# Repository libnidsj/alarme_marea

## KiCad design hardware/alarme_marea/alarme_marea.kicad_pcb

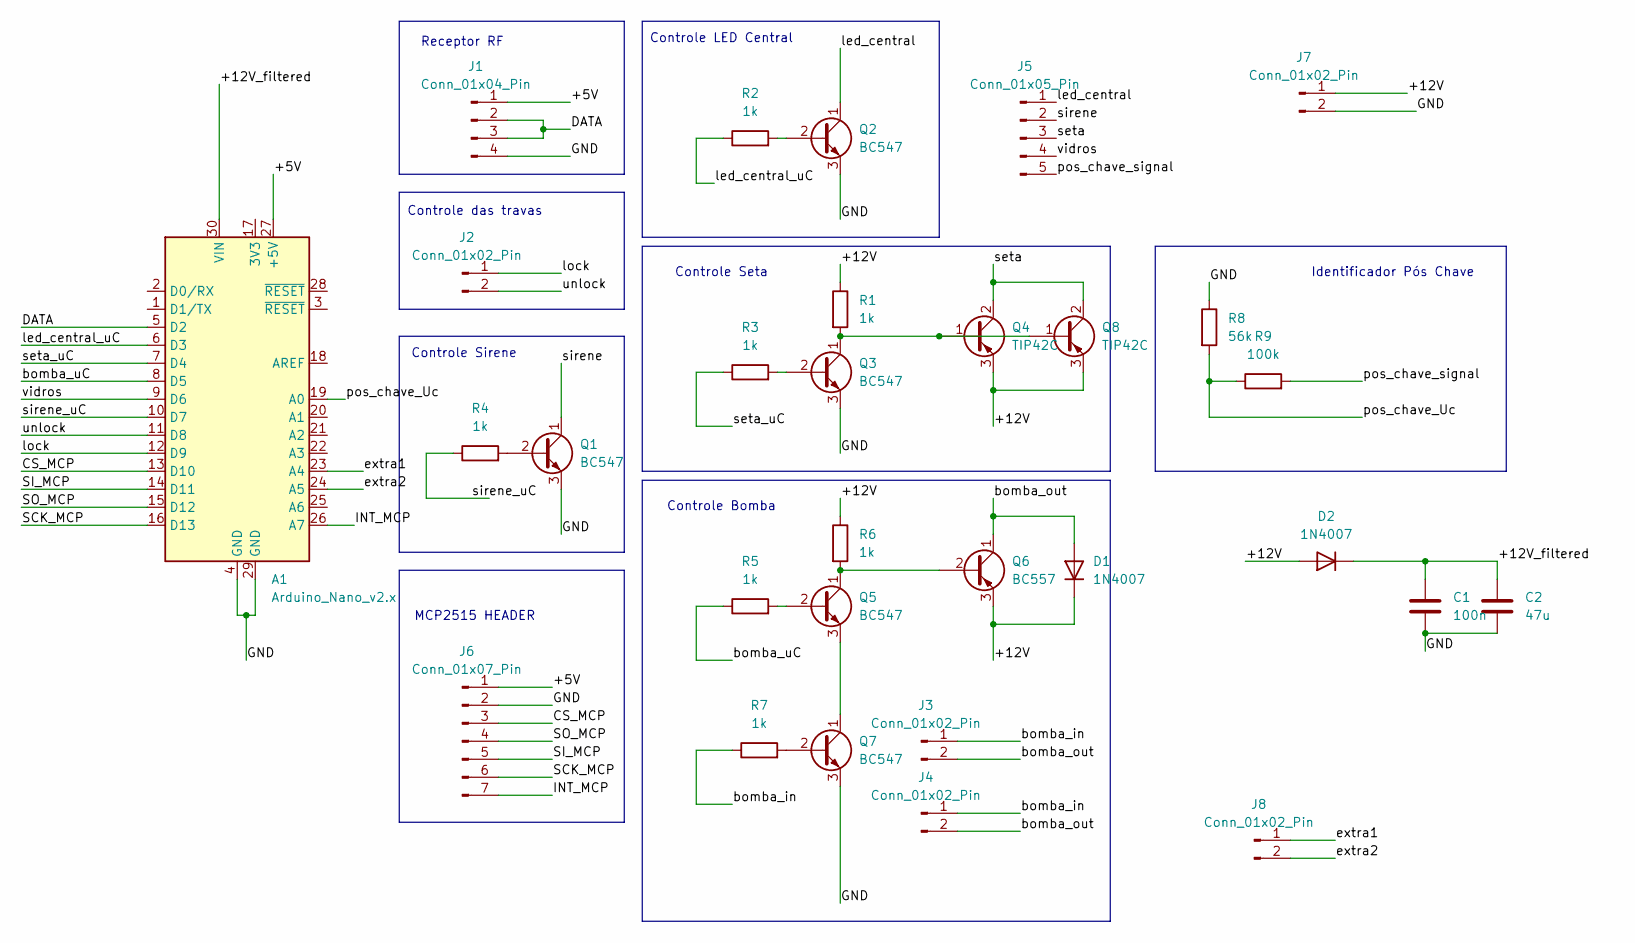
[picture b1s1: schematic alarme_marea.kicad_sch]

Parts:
A1: Arduino_Nano_v2.x; Arduino_Nano
C1: 100n; C_Disc_D5.0mm_W2.5mm_P5.00mm
C2: 47u; CP_Radial_D10.0mm_P5.00mm
D1, D2: 1N4007; D_DO-41_SOD81_P10.16mm_Horizontal
J1: Conn_01x04_Pin; PinSocket_1x04_P2.54mm_Vertical
J2, J3, J4, J7, J8: Conn_01x02_Pin; PinSocket_1x02_P2.54mm_Vertical
J5: Conn_01x05_Pin; PinHeader_1x05_P2.54mm_Vertical
J6: Conn_01x07_Pin; PinSocket_1x07_P2.54mm_Vertical
Q1, Q2, Q3, Q5, Q7: BC547; TO-92_Inline
Q4, Q8: TIP42C; TO-220-3_Vertical
Q6: BC557; TO-92_Inline
R1, R2, R3, R4, R5, R6, R7: 1k; R_Axial_DIN0207_L6.3mm_D2.5mm_P10.16mm_Horizontal
R8: 56k; R_Axial_DIN0207_L6.3mm_D2.5mm_P10.16mm_Horizontal
R9: 100k; R_Axial_DIN0207_L6.3mm_D2.5mm_P10.16mm_Horizontal

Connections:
/+5V: A1.27 (+5V), J1.1, J6.1
/+12V: D1.1 (K), D2.2 (A), J7.1, Q4.3 (E), Q6.3 (E), Q8.3 (E), R1.1, R6.1
/+12V_filtered: A1.30 (VIN), C1.1, C2.1, D2.1 (K)
/CS_MCP: A1.13 (D10), J6.3
/DATA: A1.5 (D2), J1.2, J1.3
/GND: A1.4 (GND), A1.29 (GND), C1.2, C2.2, J1.4, J6.2, J7.2, Q1.3 (E), Q2.3 (E), Q3.3 (E), Q7.3 (E), R8.1
/INT_MCP: A1.26 (A7), J6.7
/SCK_MCP: A1.16 (D13), J6.6
/SI_MCP: A1.14 (D11), J6.5
/SO_MCP: A1.15 (D12), J6.4
/bomba_in: J3.1, J4.1, R7.1
/bomba_out: D1.2 (A), J3.2, J4.2, Q6.1 (C)
/bomba_uC: A1.8 (D5), R5.1
/extra1: A1.23 (A4), J8.1
/extra2: A1.24 (A5), J8.2
/led_central: J5.1, Q2.1 (C)
/led_central_uC: A1.6 (D3), R2.1
/lock: A1.12 (D9), J2.1
/pos_chave_Uc: A1.19 (A0), R8.2, R9.1
/pos_chave_signal: J5.5, R9.2
/seta: J5.3, Q4.2 (C), Q8.2 (C)
/seta_uC: A1.7 (D4), R3.1
/sirene: J5.2, Q1.1 (C)
/sirene_uC: A1.10 (D7), R4.1
/unlock: A1.11 (D8), J2.2
/vidros: A1.9 (D6), J5.4
unnamed: Q1.2 (B), R4.2
unnamed: Q2.2 (B), R2.2
unnamed: Q3.2 (B), R3.2
unnamed: Q3.1 (C), Q4.1 (B), Q8.1 (B), R1.2
unnamed: Q5.2 (B), R5.2
unnamed: Q5.1 (C), Q6.2 (B), R6.2
unnamed: Q5.3 (E), Q7.1 (C)
unnamed: Q7.2 (B), R7.2

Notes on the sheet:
Controle LED Central
Controle Seta
MCP2515 HEADER
Identificador Pós Chave
Controle das travas
Receptor RF
Controle Sirene
Controle Bomba

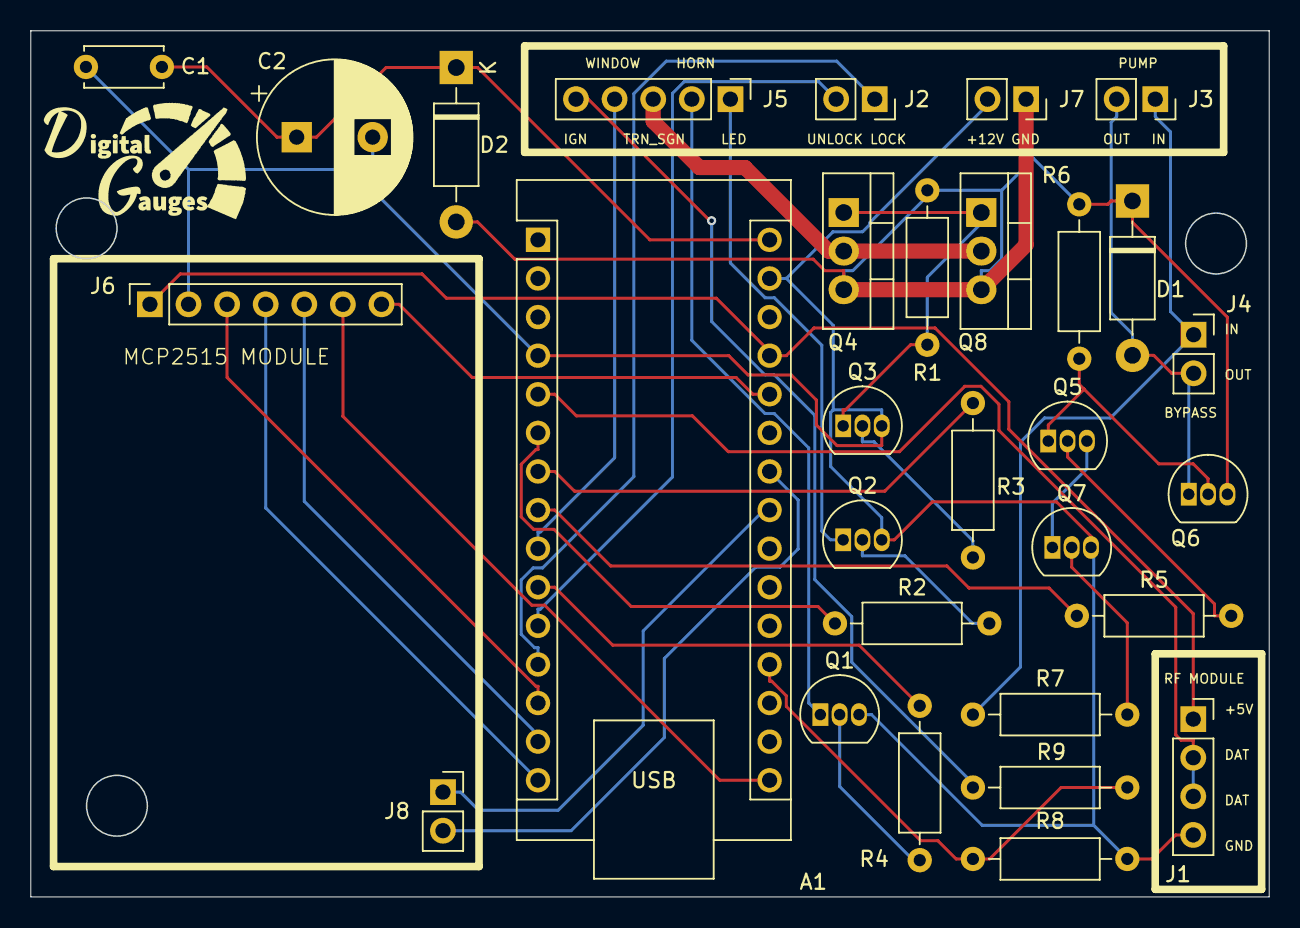
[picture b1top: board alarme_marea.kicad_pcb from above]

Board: 2 copper layers, 81.5 x 57.0 mm, 30 parts (0 on the bottom side), 34 nets.

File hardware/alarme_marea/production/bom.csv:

Designator,Footprint,Quantity,Value,LCSC Part #
A1,Arduino_Nano,1,Arduino_Nano_v2.x,
C1,C_Disc_D5.0mm_W2.5mm_P5.00mm,1,100n,
C2,CP_Radial_D10.0mm_P5.00mm,1,47u,
"D1, D2",D_DO-41_SOD81_P10.16mm_Horizontal,2,1N4007,
J1,PinSocket_1x04_P2.54mm_Vertical,1,Conn_01x04_Pin,
"J2, J3, J4, J7",PinSocket_1x02_P2.54mm_Vertical,4,Conn_01x02_Pin,
J5,PinHeader_1x05_P2.54mm_Vertical,1,Conn_01x05_Pin,
J6,PinSocket_1x07_P2.54mm_Vertical,1,Conn_01x07_Pin,
"Q1, Q2, Q3, Q5, Q7",TO-92_Inline,5,BC547,
"Q4, Q6",TO-92_Inline,2,BC557,
"R1, R2, R3, R4, R5, R6, R7",R_Axial_DIN0207_L6.3mm_D2.5mm_P10.16mm_Horizontal,7,1k,
R8,R_Axial_DIN0207_L6.3mm_D2.5mm_P10.16mm_Horizontal,1,56k,
R9,R_Axial_DIN0207_L6.3mm_D2.5mm_P10.16mm_Horizontal,1,100k,

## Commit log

2024-06-13 Initial Board Design
